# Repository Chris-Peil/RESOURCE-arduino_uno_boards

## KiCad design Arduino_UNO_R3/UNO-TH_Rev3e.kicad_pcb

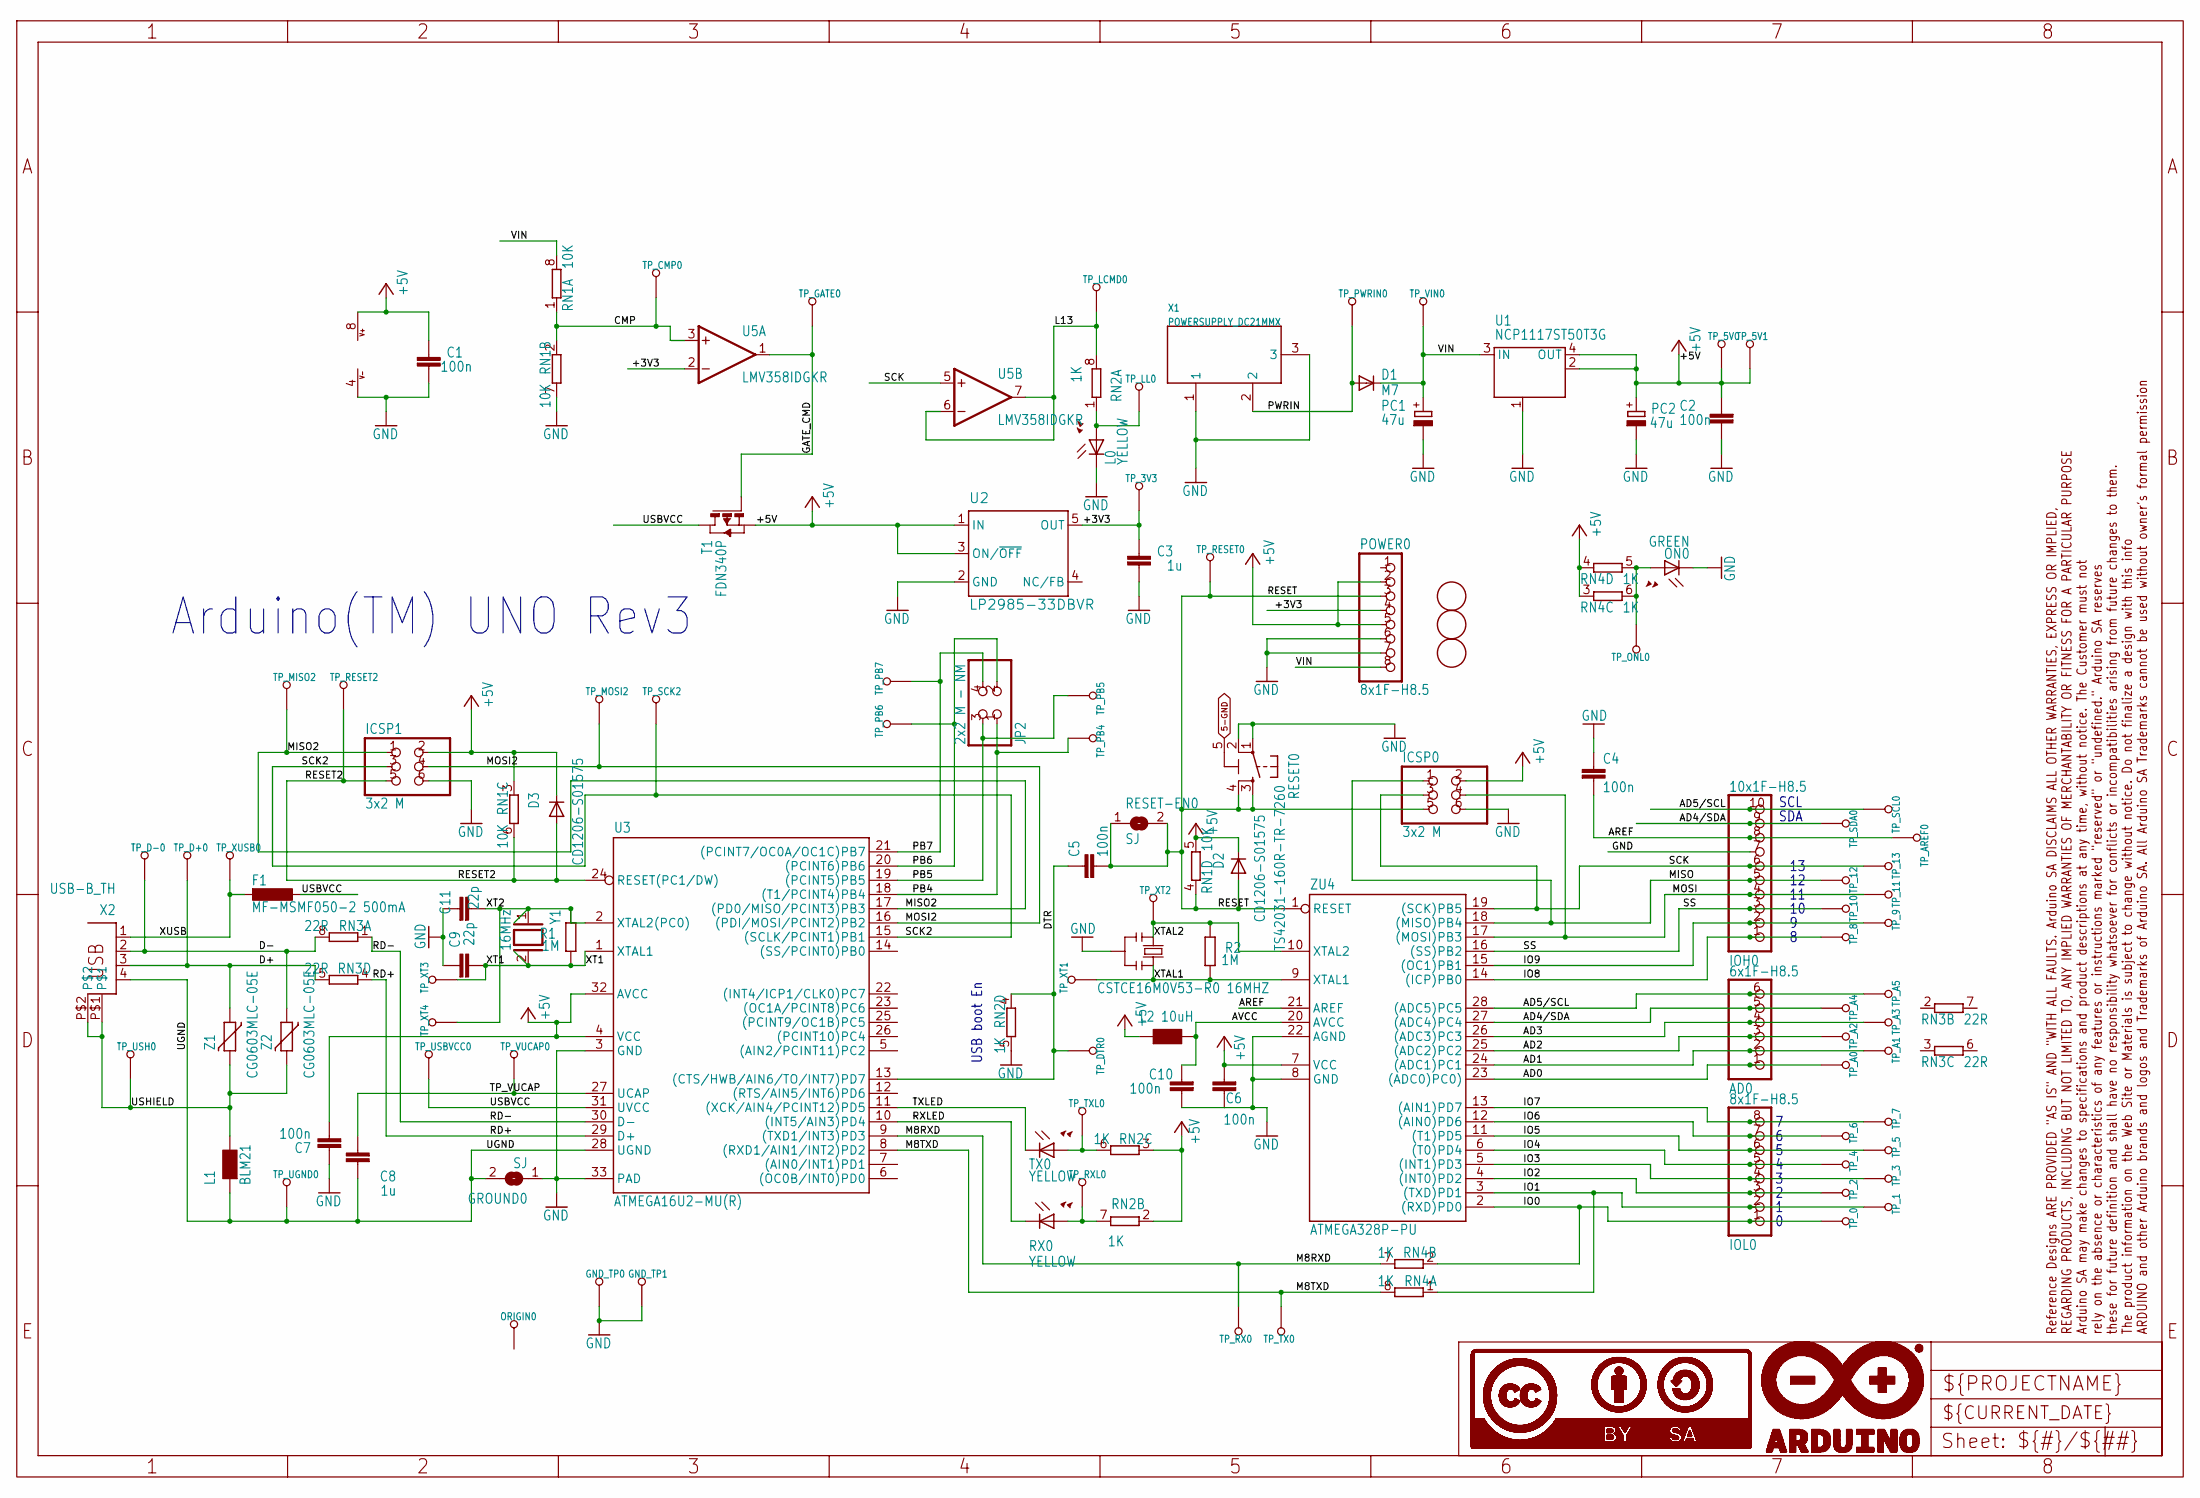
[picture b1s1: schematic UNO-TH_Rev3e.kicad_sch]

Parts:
AD0: 6x1F-H8.5; 1X06
C1, C2, C4, C5, C6, C7, C10: 100n; C0603-ROUND
C3, C8: 1u; C0603-ROUND
C9, C11: 22p; C0603-ROUND
D1: M7; SMB
D2, D3: CD1206-S01575; MINIMELF
F1: MF-MSMF050-2 500mA; L1812
FD1, FD2, FD3: FIDUCIALMOUNT; FIDUCIA-MOUNT
FRAME1: DNP; FRAME
GND_TP0, GND_TP1: TP_SP; TP-SP
GROUND0: SJ
ICSP0, ICSP1: 3x2 M; 2X03
IOH0: 10x1F-H8.5; 1X10
IOL0: 8x1F-H8.5; 1X08
JP2: 2x2 M - NM; 2X02
L0: YELLOW; CHIP-LED0805
L1: BLM21; 0805
L2: 10uH; 0805
ON0: GREEN; CHIP-LED0805
ORIGIN0: TP_SP; TP-SP
PC1, PC2: 47u; PANASONIC_D
POWER0: 8x1F-H8.5; 1X08
R1, R2: 1M; R0603-ROUND
RESET0: TS42031-160R-TR-7260; TS42
RESET-EN0: SJ
RN1: 10K; CAY16
RN2, RN4: 1K; CAY16
RN3: 22R; CAY16
RX0: YELLOW; CHIP-LED0805
T1: FDN340P; SOT-23
TP_0, TP_1, TP_2, TP_3, TP_3V3, TP_4, TP_5, TP_5V0, TP_5V1, TP_6, TP_7, TP_8, TP_9, TP_10, TP_11, TP_12, TP_13: TP_SP; TP-SP
TP_A0, TP_A1, TP_A2, TP_A3, TP_A4, TP_A5: TP_SP; TP-SP
TP_AREF0: TP_SP; TP-SP
TP_CMP0: TP_SP; TP-SP
TP_D+0: TP_SP; TP-SP
TP_D-0: TP_SP; TP-SP
TP_DTR0: TP_SP; TP-SP
TP_GATE0: TP_SP; TP-SP
TP_LCMD0: TP_SP; TP-SP
TP_LL0: TP_SP; TP-SP
TP_MISO2: TP_SP; TP-SP
TP_MOSI2: TP_SP; TP-SP
TP_ONL0: TP_SP; TP-SP
TP_PB4, TP_PB5, TP_PB6, TP_PB7: TP_SP; TP-SP
TP_PWRIN0: TP_SP; TP-SP
TP_RESET0, TP_RESET2: TP_SP; TP-SP
TP_RX0: TP_SP; TP-SP
TP_RXL0: TP_SP; TP-SP
TP_SCK2: TP_SP; TP-SP
TP_SCL0: TP_SP; TP-SP
TP_SDA0: TP_SP; TP-SP
TP_TX0: TP_SP; TP-SP
TP_TXL0: TP_SP; TP-SP
TP_UGND0: TP_SP; TP-SP
TP_USBVCC0: TP_SP; TP-SP
TP_USH0: TP_SP; TP-SP
TP_VIN0: TP_SP; TP-SP
TP_VUCAP0: TP_SP; TP-SP
TP_XT1, TP_XT2, TP_XT3, TP_XT4: TP_SP; TP-SP
TP_XUSB0: TP_SP; TP-SP
TX0: YELLOW; CHIP-LED0805
U1: NCP1117ST50T3G; SOT223
U2: LP2985-33DBVR; SOT23-DBV
U3: ATMEGA16U2-MU(R); MLF32
U5: LMV358IDGKR; MSOP08
X1: POWERSUPPLY_DC21MMX; POWERSUPPLY_DC-21MM
X2: USB-B_TH; PN61729
Y1: 16MHz; QS
Y2: CSTCE16M0V53-R0 16MHZ; RESONATOR
Z1, Z2: CG0603MLC-05E; CT_CN0603
ZU4: ATMEGA328P-PU; DIL28-3

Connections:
5-GND: RESET0.5 (5-GND)
+3V3: C3.2, POWER0.4, TP_3V3.X, U2.5 (OUT), U5.2 (-IN)
+5V: C1.2, C2.2, C6.2, C7.1, D2.C, D3.C, ICSP0.2, ICSP1.2, L2.1, PC2.+, POWER0.2, POWER0.5, RN1.3 (1), RN1.5 (2), RN2.2 (1), RN2.3 (1), RN4.3 (1), RN4.4 (1), T1.2 (S), TP_5V0.X, TP_5V1.X, U1.2 (OUT@1), U1.4 (OUT), U2.1 (IN), U2.3 (ON/~OFF), U3.4 (VCC), U3.32 (AVCC), U5.8 (V+), ZU4.7 (VCC)
AD0: AD0.1, TP_A0.X, ZU4.23 ((ADC0)PC0))
AD1: AD0.2, TP_A1.X, ZU4.24 ((ADC1)PC1)
AD2: AD0.3, TP_A2.X, ZU4.25 ((ADC2)PC2)
AD3: AD0.4, TP_A3.X, ZU4.26 ((ADC3)PC3)
AD4/SDA: AD0.5, IOH0.9, TP_A4.X, TP_SDA0.X, ZU4.27 ((ADC4)PC4)
AD5/SCL: AD0.6, IOH0.10, TP_A5.X, TP_SCL0.X, ZU4.28 ((ADC5)PC5)
AREF: C4.2, IOH0.8, TP_AREF0.X, ZU4.21 (AREF)
AVCC: C10.2, L2.2, ZU4.20 (AVCC)
CMP: RN1.1, RN1.2 (1), TP_CMP0.X, U5.3 (+IN)
D+: RN3.5 (2), TP_D+0.X, X2.3, Z1.1
D-: RN3.8 (2), TP_D-0.X, X2.2, Z2.1
DTR: C5.1, RN2.4 (1), TP_DTR0.X, U3.13 ((CTS/HWB/AIN6/TO/INT7)PD7)
GATE_CMD: T1.3 (G), TP_GATE0.X, U5.1 (OUT)
GND: C1.1, C2.1, C3.1, C4.1, C6.1, C7.2, C9.2, C10.1, C11.2, GND_TP0.X, GND_TP1.X, GROUND0.1, ICSP0.6, ICSP1.6, IOH0.7, L0.C, ON0.C, PC1.-, PC2.-, POWER0.6, POWER0.7, RESET0.1, RESET0.2, RN1.7 (2), RN2.5 (2), U1.1 (GND/ADJ), U2.2 (GND), U3.3 (GND), U3.33 (PAD), U5.4 (V-), X1.1, X1.3, Y2.2, ZU4.8 (GND), ZU4.22 (AGND)
IO0: IOL0.1, RN4.2 (1), TP_0.X, ZU4.2 ((RXD)PD0)
IO1: IOL0.2, RN4.1, TP_1.X, ZU4.3 ((TXD)PD1)
IO2: IOL0.3, TP_2.X, ZU4.4 ((INT0)PD2)
IO3: IOL0.4, TP_3.X, ZU4.5 ((INT1)PD3)
IO4: IOL0.5, TP_4.X, ZU4.6 ((T0)PD4)
IO5: IOL0.6, TP_5.X, ZU4.11 ((T1)PD5)
IO6: IOL0.7, TP_6.X, ZU4.12 ((AIN0)PD6)
IO7: IOL0.8, TP_7.X, ZU4.13 ((AIN1)PD7)
IO8: IOH0.1, TP_8.X, ZU4.14 ((ICP)PB0)
IO9: IOH0.2, TP_9.X, ZU4.15 ((OC1)PB1)
L13: RN2.8 (2), TP_LCMD0.X, U5.6 (-IN), U5.7 (OUT)
M8RXD: RN4.7 (2), TP_RX0.X, U3.9 ((TXD1/INT3)PD3)
M8TXD: RN4.8 (2), TP_TX0.X, U3.8 ((RXD1/AIN1/INT2)PD2)
MISO: ICSP0.1, IOH0.5, TP_12.X, ZU4.18 ((MISO)PB4)
MISO2: ICSP1.1, TP_MISO2.X, U3.17 ((PD0/MISO/PCINT3)PB3)
MOSI: ICSP0.4, IOH0.4, TP_11.X, ZU4.17 ((MOSI)PB3)
MOSI2: ICSP1.4, TP_MOSI2.X, U3.16 ((PDI/MOSI/PCINT2)PB2)
unnamed: L0.A, RN2.1, TP_LL0.X
unnamed: ON0.A, RN4.5 (2), RN4.6 (2), TP_ONL0.X
unnamed: RN2.7 (2), RX0.A, TP_RXL0.X
unnamed: RN2.6 (2), TP_TXL0.X, TX0.A
PB4: JP2.1, TP_PB4.X, U3.18 ((T1/PCINT4)PB4)
PB5: JP2.3, TP_PB5.X, U3.19 ((PCINT5)PB5)
PB6: JP2.2, TP_PB6.X, U3.20 ((PCINT6)PB6)
PB7: JP2.4, TP_PB7.X, U3.21 ((PCINT7/OC0A/OC1C)PB7)
PWRIN: D1.A, TP_PWRIN0.X, X1.2
RD+: RN3.4 (1), U3.29 (D+)
RD-: RN3.1, U3.30 (D-)
RESET: C5.2, D2.A, ICSP0.5, POWER0.3, RESET0.3, RESET0.4, RESET-EN0.1, RESET-EN0.2, RN1.4 (1), TP_RESET0.X, ZU4.1 (RESET)
RESET2: D3.A, ICSP1.5, RN1.6 (2), TP_RESET2.X, U3.24 (RESET(PC1/DW))
RXLED: RX0.C, U3.10 ((INT5/AIN3)PD4)
SCK: ICSP0.3, IOH0.6, TP_13.X, U5.5 (+IN), ZU4.19 ((SCK)PB5)
SCK2: ICSP1.3, TP_SCK2.X, U3.15 ((SCLK/PCINT1)PB1)
SS: IOH0.3, TP_10.X, ZU4.16 ((SS)PB2)
TP_VUCAP: C8.1, TP_VUCAP0.X, U3.27 (UCAP)
TXLED: TX0.C, U3.11 ((XCK/AIN4/PCINT12)PD5)
UGND: C8.2, GROUND0.2, L1.1, TP_UGND0.X, U3.28 (UGND), X2.4
USBVCC: F1.1, T1.1 (D), TP_USBVCC0.X, U3.31 (UVCC)
USHIELD: L1.2, TP_USH0.X, X2.P$1, X2.P$2, Z1.2, Z2.2
VIN: D1.C, PC1.+, POWER0.8, RN1.8 (2), TP_VIN0.X, U1.3 (IN)
XT1: C9.1, R1.1, TP_XT3.X, U3.1 (XTAL1), Y1.2
XT2: C11.1, R1.2, TP_XT4.X, U3.2 (XTAL2(PC0)), Y1.1
XTAL1: R2.1, TP_XT1.X, Y2.3, ZU4.9 (XTAL1)
XTAL2: R2.2, TP_XT2.X, Y2.1, ZU4.10 (XTAL2)
XUSB: F1.2, TP_XUSB0.X, X2.1

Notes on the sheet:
Arduino(TM) UNO Rev3
SCL
SDA
USB boot En

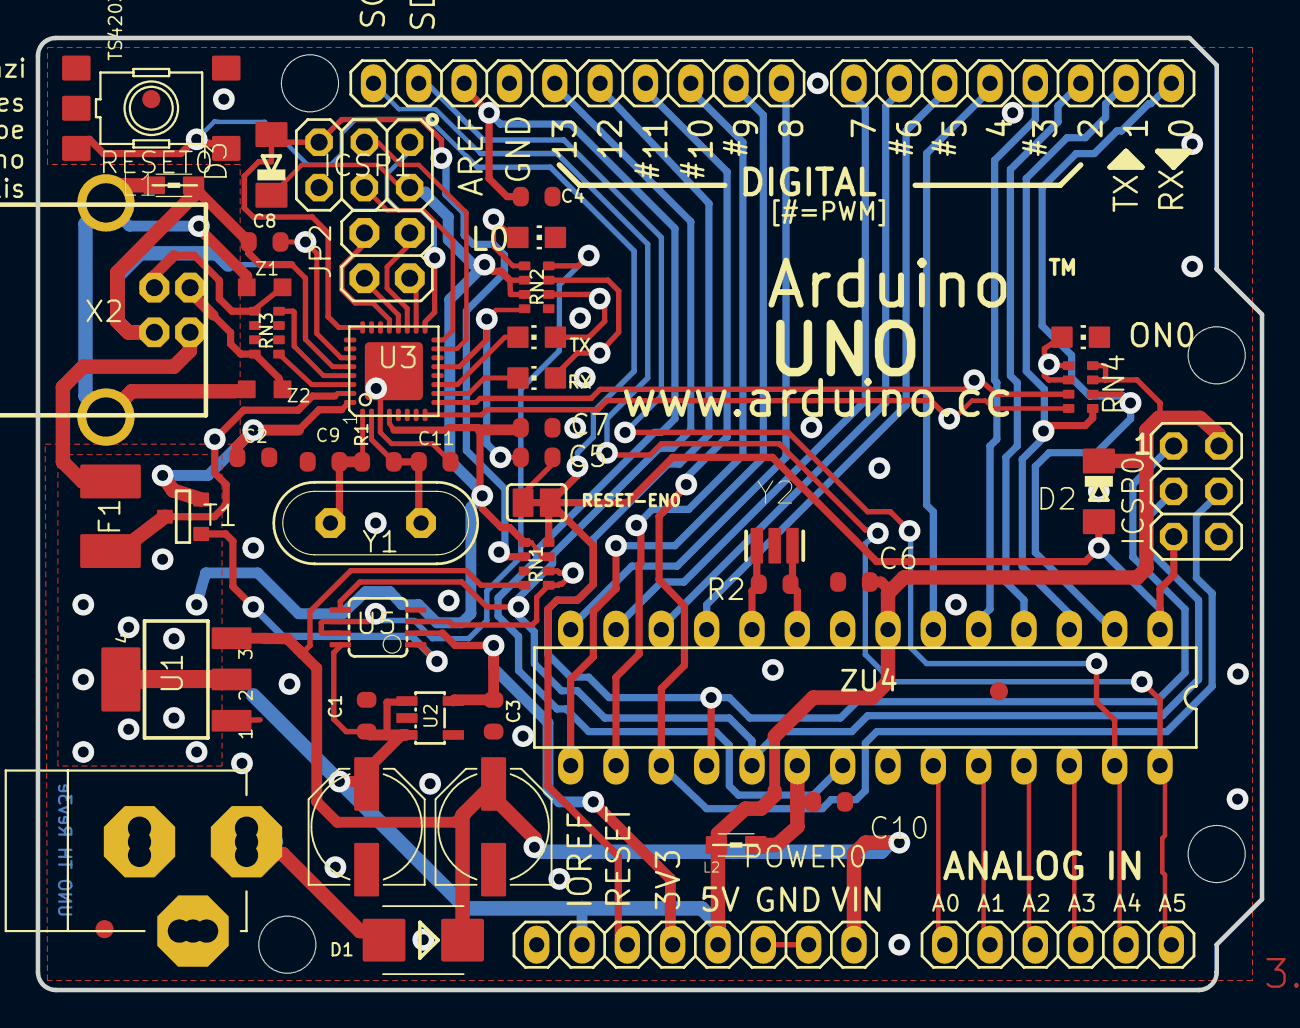
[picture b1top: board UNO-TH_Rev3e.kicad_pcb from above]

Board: 2 copper layers, 68.6 x 53.3 mm, 120 parts (1 on the bottom side), 61 nets.

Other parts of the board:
UNK_HOLE_0: dummyfp0
UNK_HOLE_1: dummyfp1
UNK_HOLE_2: dummyfp2
UNK_HOLE_3: dummyfp3

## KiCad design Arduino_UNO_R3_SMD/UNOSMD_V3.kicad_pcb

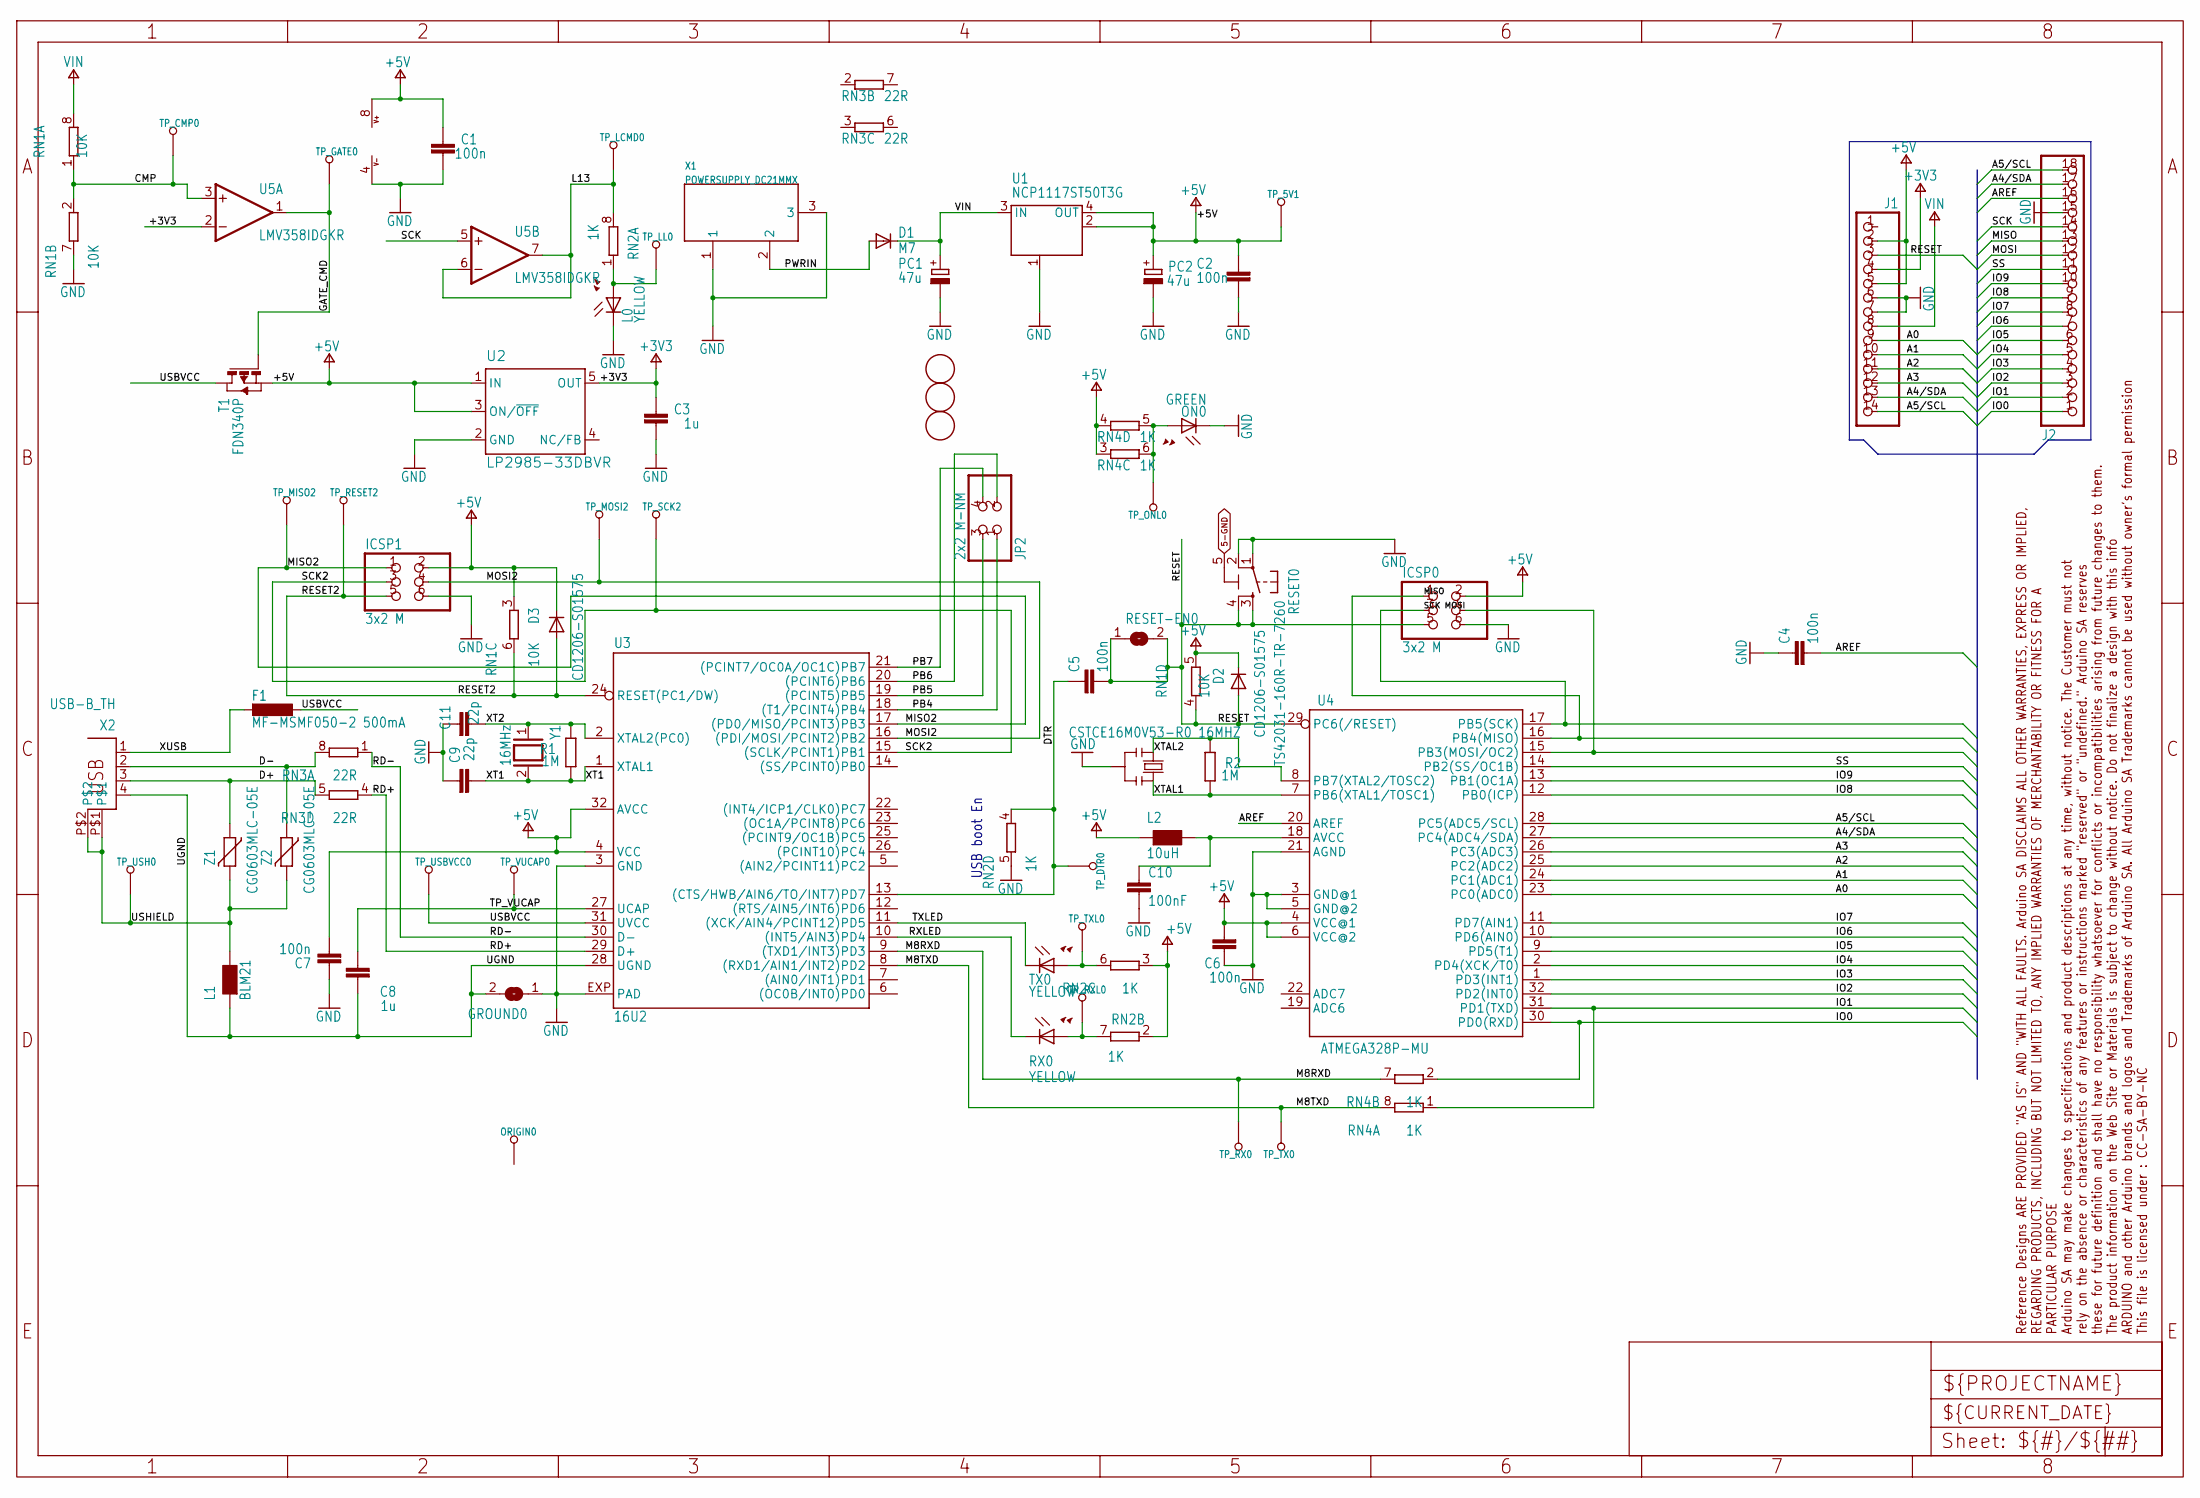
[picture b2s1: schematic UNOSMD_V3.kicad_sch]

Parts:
C1, C2, C4, C5, C6, C7: 100n; C0603-ROUND
C3, C8: 1u; C0603-ROUND
C9, C11: 22p; C0603-ROUND
C10: 100nF; C0603-ROUND
D1: M7; SMB
D2, D3: CD1206-S01575; MINIMELF
F1: MF-MSMF050-2 500mA; L1812
FD1, FD2, FD3: DNP; FD-1-1.5
FRAME1: DNP; FRAME
GROUND0: SJ
ICSP0, ICSP1: 3x2 M; 2X03
J1: -; 1X14-CUSTOM
J2: -; 1X18-CUSTOM
JP2: 2x2 M-NM; 2X02
L0: YELLOW; CHIP-LED0805
L1: BLM21; 0805
L2: 10uH; 0805
ON0: GREEN; CHIP-LED0805
ORIGIN0: TP_SP; TP-SP
PC1, PC2: 47u; PANASONIC_D
R1, R2: 1M; R0603-ROUND
RESET0: TS42031-160R-TR-7260; TS42
RESET-EN0: SJ
RN1: 10K; CAY16
RN2, RN4: 1K; CAY16
RN3: 22R; CAY16
RX0: YELLOW; CHIP-LED0805
T1: FDN340P; SOT-23
TP_5V1: TP_SP; TP-SP
TP_CMP0: TP_SP; TP-SP
TP_DTR0: TP_SP; TP-SP
TP_GATE0: TP_SP; TP-SP
TP_LCMD0: TP_SP; TP-SP
TP_LL0: TP_SP; TP-SP
TP_MISO2: TP_SP; TP-SP
TP_MOSI2: TP_SP; TP-SP
TP_ONL0: TP_SP; TP-SP
TP_RESET2: TP_SP; TP-SP
TP_RX0: TP_SP; TP-SP
TP_RXL0: TP_SP; TP-SP
TP_SCK2: TP_SP; TP-SP
TP_TX0: TP_SP; TP-SP
TP_TXL0: TP_SP; TP-SP
TP_USBVCC0: TP_SP; TP-SP
TP_USH0: TP_SP; TP-SP
TP_VUCAP0: TP_SP; TP-SP
TX0: YELLOW; CHIP-LED0805
U1: NCP1117ST50T3G; SOT223
U2: LP2985-33DBVR; SOT23-DBV
U3: 16U2; ATMEL_QFN32
U4: ATMEGA328P-MU; MLF32
U5: LMV358IDGKR; MSOP08
X1: POWERSUPPLY_DC21MMX; POWERSUPPLY_DC-21MM
X2: USB-B_TH; PN61729
Y1: 16MHz; QS
Y2: CSTCE16M0V53-R0 16MHZ; RESONATOR
Z1, Z2: CG0603MLC-05E; CT_CN0603

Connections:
5-GND: RESET0.5 (5-GND)
+3V3: C3.2, J1.4, U2.5 (OUT), U5.2 (-IN)
+5V: C1.2, C2.2, C6.2, C7.1, D2.C, D3.C, ICSP0.2, ICSP1.2, J1.2, J1.5, L2.1, PC2.+, RN1.3 (1), RN1.5 (2), RN2.2 (1), RN2.3 (1), RN4.3 (1), RN4.4 (1), T1.2 (S), TP_5V1.X, U1.2 (OUT@1), U1.4 (OUT), U2.1 (IN), U2.3 (ON/~OFF), U3.4 (VCC), U3.32 (AVCC), U4.4 (VCC@1), U4.6 (VCC@2), U5.8 (V+)
A0: J1.9, U4.23 (PC0(ADC0))
A1: J1.10, U4.24 (PC1(ADC1))
A2: J1.11, U4.25 (PC2(ADC2))
A3: J1.12, U4.26 (PC3(ADC3))
A4/SDA: J1.13, J2.17, U4.27 (PC4(ADC4/SDA))
A5/SCL: J1.14, J2.18, U4.28 (PC5(ADC5/SCL))
AREF: C4.2, J2.16, U4.20 (AREF)
CMP: RN1.1, RN1.2 (1), TP_CMP0.X, U5.3 (+IN)
D+: RN3.5 (2), X2.3, Z1.1
D-: RN3.8 (2), X2.2, Z2.1
DTR: C5.1, RN2.4 (1), TP_DTR0.X, U3.13 ((CTS/HWB/AIN6/TO/INT7)PD7)
GATE_CMD: T1.3 (G), TP_GATE0.X, U5.1 (OUT)
GND: C1.1, C2.1, C3.1, C4.1, C6.1, C7.2, C9.2, C10.2, C11.2, GROUND0.1, ICSP0.6, ICSP1.6, J1.6, J1.7, J2.15, L0.C, ON0.C, PC1.-, PC2.-, RESET0.1, RESET0.2, RN1.7 (2), RN2.5 (2), U1.1 (GND/ADJ), U2.2 (GND), U3.3 (GND), U3.EXP (PAD), U4.3 (GND@1), U4.5 (GND@2), U4.21 (AGND), U5.4 (V-), X1.1, X1.3, Y2.2
IO0: J2.1, RN4.2 (1), U4.30 (PD0(RXD))
IO1: J2.2, RN4.1, U4.31 (PD1(TXD))
IO2: J2.3, U4.32 (PD2(INT0))
IO3: J2.4, U4.1 (PD3(INT1))
IO4: J2.5, U4.2 (PD4(XCK/T0))
IO5: J2.6, U4.9 (PD5(T1))
IO6: J2.7, U4.10 (PD6(AIN0))
IO7: J2.8, U4.11 (PD7(AIN1))
IO8: J2.9, U4.12 (PB0(ICP))
IO9: J2.10, U4.13 (PB1(OC1A))
L13: RN2.8 (2), TP_LCMD0.X, U5.6 (-IN), U5.7 (OUT)
M8RXD: RN4.7 (2), TP_RX0.X, U3.9 ((TXD1/INT3)PD3)
M8TXD: RN4.8 (2), TP_TX0.X, U3.8 ((RXD1/AIN1/INT2)PD2)
MISO: ICSP0.1, J2.13, U4.16 (PB4(MISO))
MISO2: ICSP1.1, TP_MISO2.X, U3.17 ((PD0/MISO/PCINT3)PB3)
MOSI: ICSP0.4, J2.12, U4.15 (PB3(MOSI/OC2))
MOSI2: ICSP1.4, TP_MOSI2.X, U3.16 ((PDI/MOSI/PCINT2)PB2)
unnamed: L0.A, RN2.1, TP_LL0.X
unnamed: ON0.A, RN4.5 (2), RN4.6 (2), TP_ONL0.X
unnamed: C10.1, L2.2, U4.18 (AVCC)
unnamed: RN2.7 (2), RX0.A, TP_RXL0.X
unnamed: RN2.6 (2), TP_TXL0.X, TX0.A
PB4: JP2.1, U3.18 ((T1/PCINT4)PB4)
PB5: JP2.3, U3.19 ((PCINT5)PB5)
PB6: JP2.2, U3.20 ((PCINT6)PB6)
PB7: JP2.4, U3.21 ((PCINT7/OC0A/OC1C)PB7)
PWRIN: D1.A, X1.2
RD+: RN3.4 (1), U3.29 (D+)
RD-: RN3.1, U3.30 (D-)
RESET: C5.2, D2.A, ICSP0.5, J1.3, RESET0.3, RESET0.4, RESET-EN0.1, RESET-EN0.2, RN1.4 (1), U4.29 (PC6(/RESET))
RESET2: D3.A, ICSP1.5, RN1.6 (2), TP_RESET2.X, U3.24 (RESET(PC1/DW))
RXLED: RX0.C, U3.10 ((INT5/AIN3)PD4)
SCK: ICSP0.3, J2.14, U4.17 (PB5(SCK)), U5.5 (+IN)
SCK2: ICSP1.3, TP_SCK2.X, U3.15 ((SCLK/PCINT1)PB1)
SS: J2.11, U4.14 (PB2(SS/OC1B))
TP_VUCAP: C8.1, TP_VUCAP0.X, U3.27 (UCAP)
TXLED: TX0.C, U3.11 ((XCK/AIN4/PCINT12)PD5)
UGND: C8.2, GROUND0.2, L1.1, U3.28 (UGND), X2.4
USBVCC: F1.1, T1.1 (D), TP_USBVCC0.X, U3.31 (UVCC)
USHIELD: L1.2, TP_USH0.X, X2.P$1, X2.P$2, Z1.2, Z2.2
VIN: D1.C, J1.8, PC1.+, RN1.8 (2), U1.3 (IN)
XT1: C9.1, R1.1, U3.1 (XTAL1), Y1.2
XT2: C11.1, R1.2, U3.2 (XTAL2(PC0)), Y1.1
XTAL1: R2.1, U4.7 (PB6(XTAL1/TOSC1)), Y2.3
XTAL2: R2.2, U4.8 (PB7(XTAL2/TOSC2)), Y2.1
XUSB: F1.2, X2.1

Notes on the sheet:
USB boot En

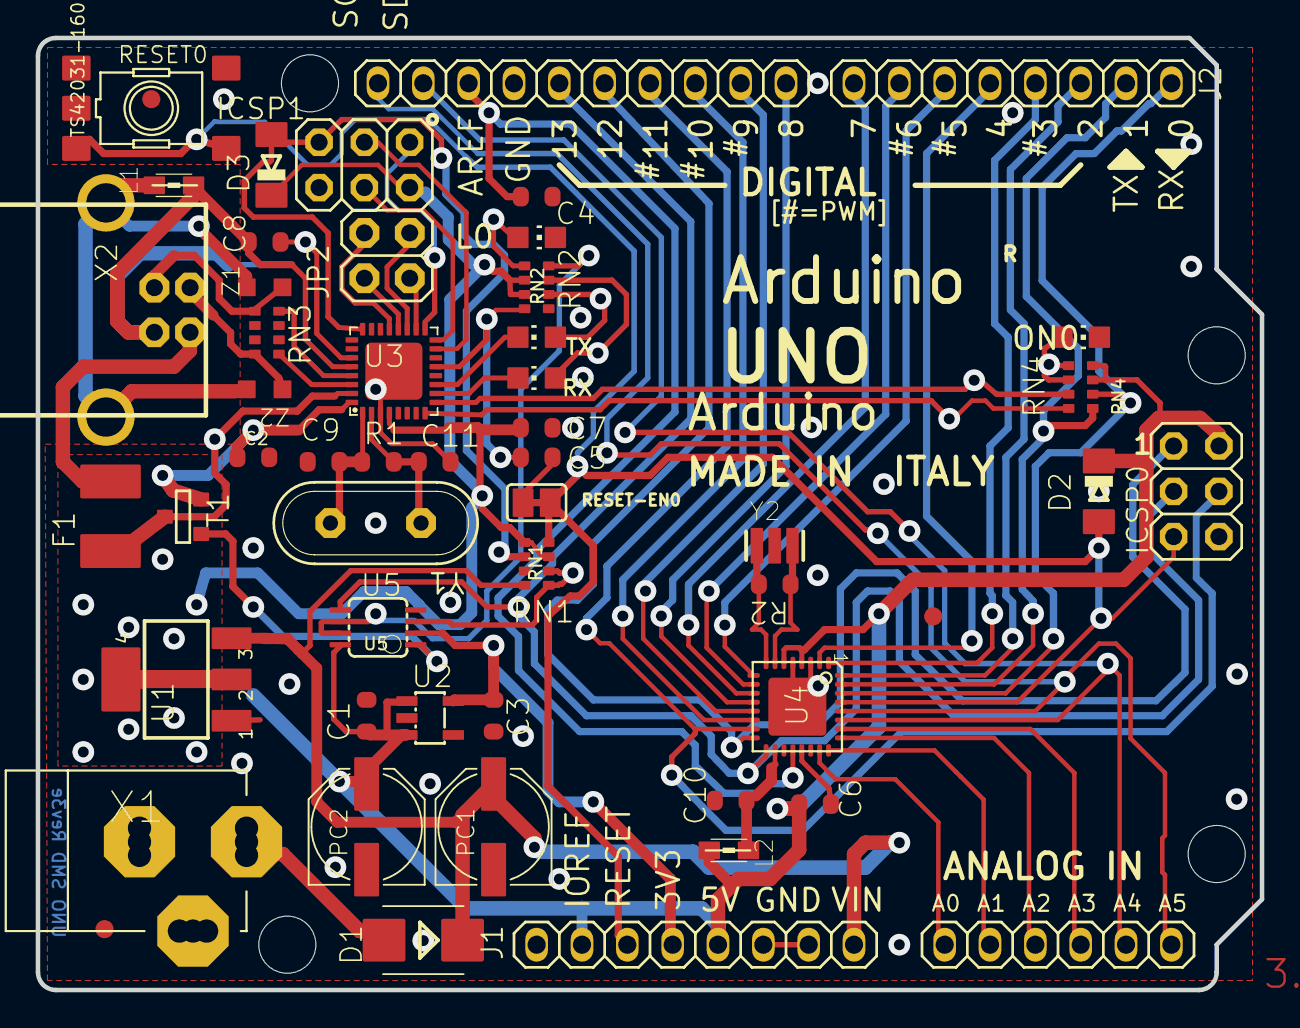
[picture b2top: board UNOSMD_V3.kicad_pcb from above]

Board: 2 copper layers, 68.6 x 53.3 mm, 76 parts (1 on the bottom side), 61 nets.

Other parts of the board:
UNK_HOLE_0: dummyfp0
UNK_HOLE_1: dummyfp1
UNK_HOLE_2: dummyfp2
UNK_HOLE_3: dummyfp3

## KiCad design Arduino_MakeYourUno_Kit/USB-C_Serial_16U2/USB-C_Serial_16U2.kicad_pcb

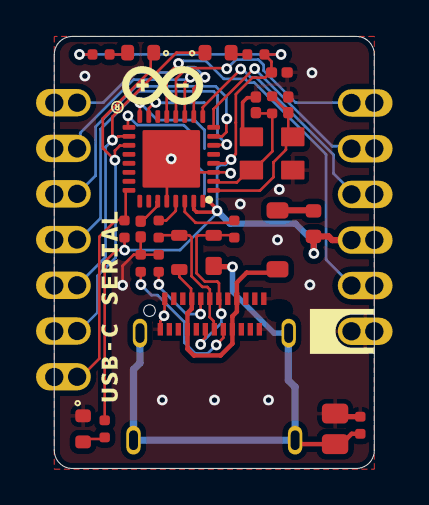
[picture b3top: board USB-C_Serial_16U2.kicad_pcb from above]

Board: 2 copper layers, 17.8 x 24.0 mm, 27 parts (1 on the bottom side), 31 nets.

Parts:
C1: C0402C105K8PACTU; CAP-0402
C2: C0805C472KDRACTU; CAP-0805
C3, C4: C0402H100J5GACTU; CAP-0402
C5: C0402C104K4RACTU; CAP-0402
D1: PRTR5V0U2X,215; SOT190P230X110-4N
D2: PMEG6020AELRX; SOD123-1
DL1, DL2: HSMD-C190; LEDC1608X80N-AK
DL3: HSMG-C190; LEDC1608X80N-AK
ICPS1: PINHD-2X03-SM-TP; 2X03-TP
J1: 12401598E4#2A
J2: PH1-07-UA; CONN STRIP 2.54 PIN HEADER DIP 180° 1x 7 PIN GOLD FLASH cas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
J3: PH1-06-UA; CONN STRP 2.54 PIN HEADER DIP 180° 1x X PIN GOLD FLASH
L1: BLM18PG471SN1D; L-0603
R1, R2: RC0402FR-075K1L; RES-0402
R3, R6: CRCW04021M00FKED; RES-0402
R4, R5: CRCW040222R0JNEDC; RES-0402
R7: CRCW040210K0FKED; RES-0402
R8, R9, R10: CRCW0402330RJNED; RES-0402
U1: ATMEGA16U2; ATMEL_QFN32
Y1: FTX16.000M12SM3S-30/30; CX3225SB16000D0GZJC1-Footprint-1

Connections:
CD: J2.4, U1.6
CTS: J3.2, U1.13
D+: D1.3, J1.A6, J1.B6, R5.1
D-: D1.2, J1.A7, J1.B7, R4.1
DSR: J2.2, U1.11
DTR: J2.1, U1.10
GND: C1.2, C2.1, C3.1, C4.1, C5.1, DL3.C, J1.A1, J1.A12, J1.B1, J1.B12, J3.1, R1.1, R2.2, R3.1, U1.3, U1.28, U1.EXP, Y1.2, Y1.4
LED_RX: DL1.C, J2.5, U1.18
LED_TX: DL2.C, J2.6, U1.19
MISO: ICPS1.5, U1.17
MOSI: ICPS1.3, U1.16
NetC1_1: C1.1, U1.27
NetC2_2: C2.2, D1.1, J1.SHIELD 1, J1.SHIELD 2, J1.SHIELD 3, J1.SHIELD 4, R3.2
NetC3_2: C3.2, R6.2, U1.2, Y1.3
NetC4_2: C4.2, R6.1, U1.1, Y1.1
NetD2_C: D2.C, L1.1
NetDL1_A: DL1.A, R9.1
NetDL2_A: DL2.A, R8.2
NetDL3_A: DL3.A, R10.1
NetJ1_A5: J1.A5, R1.2
NetJ1_B5: J1.B5, R2.1
NetR4_2: R4.2, U1.30
NetR5_2: R5.2, U1.29
RI: J2.3, U1.7
RST: J2.7, R7.1, U1.24
RTS: J3.6, U1.12
RXD: J3.5, U1.8
SCLK: ICPS1.1, U1.15
TXD: J3.4, U1.9
VBUS: D1.4, D2.A, J1.A4, J1.A9, J1.B4, J1.B9
VCC: C5.2, J3.3, L1.2, R7.2, R8.1, R9.2, R10.2, U1.4, U1.31, U1.32

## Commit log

2025-12-07 +DIY UNO, +UNO R3, +UNO R3 SMD, +UNO WiFi
2025-12-07 added datasheet and header details for R3

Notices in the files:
Arduino_UNO_R3_SMD/UNOSMD_V3.kicad_sch:
This file is licensed under : CC-SA-BY-NC
